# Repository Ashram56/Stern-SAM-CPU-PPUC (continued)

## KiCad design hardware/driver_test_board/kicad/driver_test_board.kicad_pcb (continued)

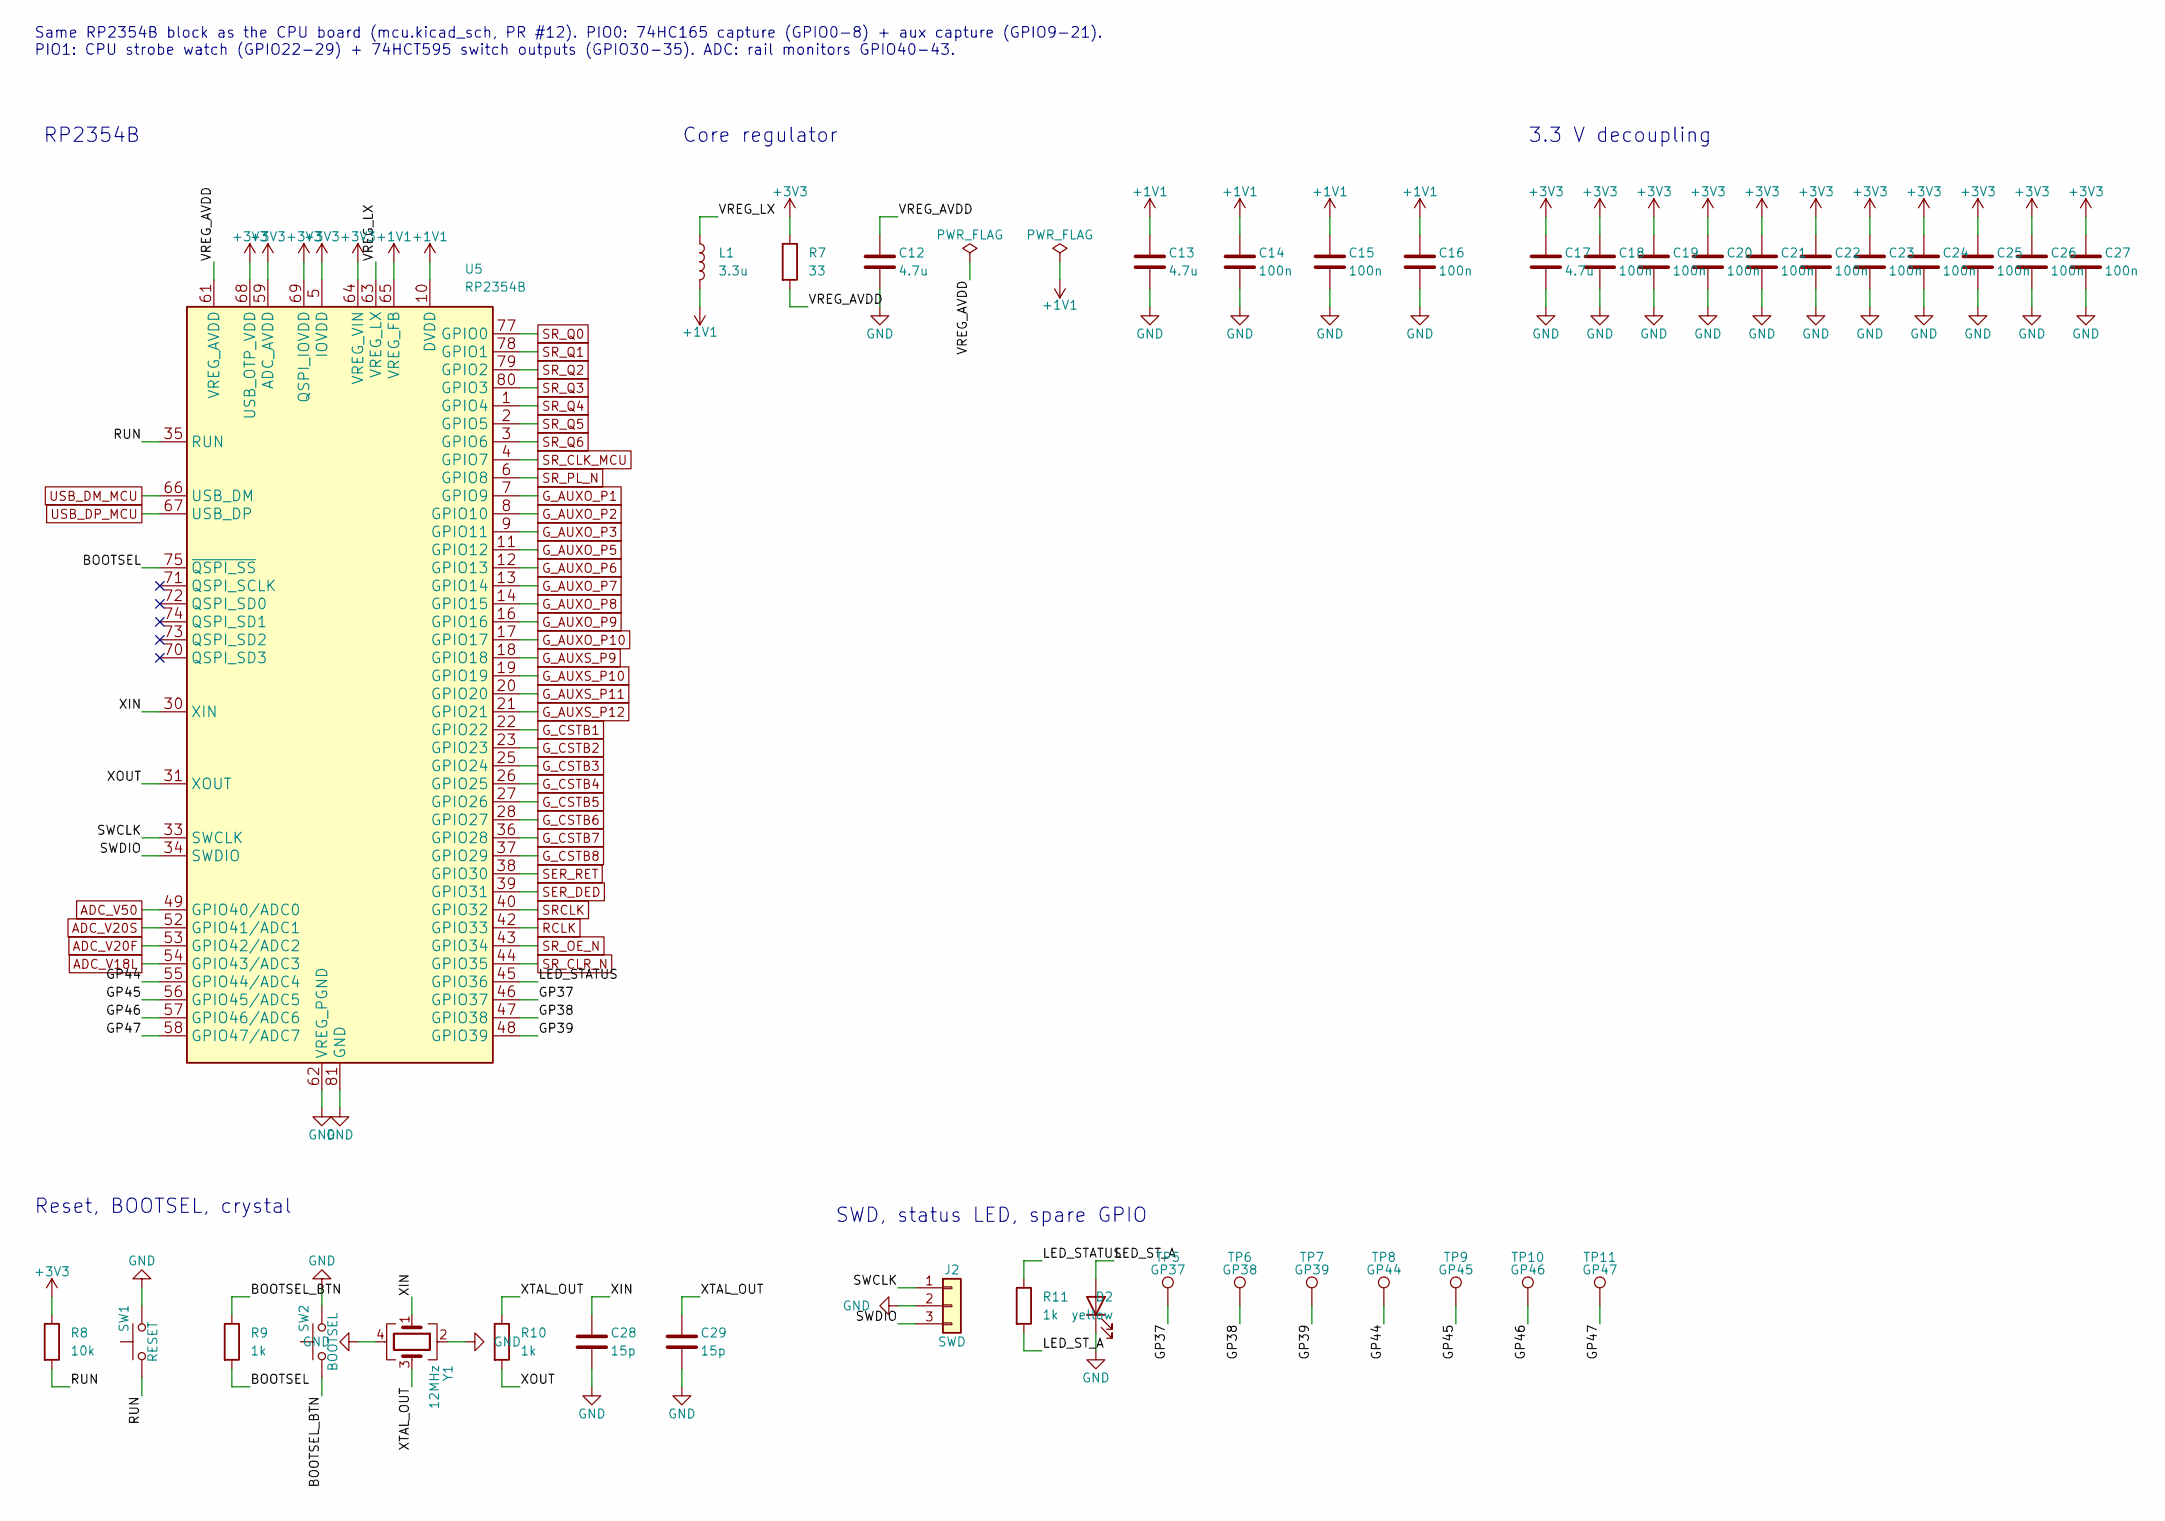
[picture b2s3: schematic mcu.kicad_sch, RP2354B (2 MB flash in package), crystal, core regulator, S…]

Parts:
C12, C13, C17: 4.7u; C_0805_2012Metric
C14, C15, C16, C18, C19, C20, C21, C22, C23, C24, C25, C26, C27: 100n; C_0805_2012Metric
C28, C29: 15p; C_0805_2012Metric
D2: yellow; LED_0805_2012Metric
J2: SWD; PinHeader_1x03_P2.54mm_Vertical
L1: 3.3u; L_Cenker_CKCS201610
R7: 33; R_0805_2012Metric
R8: 10k; R_0805_2012Metric
R9, R10, R11: 1k; R_0805_2012Metric
SW1: RESET; SW_SPST_TL3342
SW2: BOOTSEL; SW_SPST_TL3342
TP5: GP37; TestPoint_Pad_D1.5mm
TP6: GP38; TestPoint_Pad_D1.5mm
TP7: GP39; TestPoint_Pad_D1.5mm
TP8: GP44; TestPoint_Pad_D1.5mm
TP9: GP45; TestPoint_Pad_D1.5mm
TP10: GP46; TestPoint_Pad_D1.5mm
TP11: GP47; TestPoint_Pad_D1.5mm
U5: RP2354B; QFN-80-1EP_10x10mm_P0.4mm_EP3.4x3.4mm
Y1: 12MHz; Crystal_SMD_3225-4Pin_3.2x2.5mm

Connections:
+1V1: C13.1, C14.1, C15.1, C16.1, L1.2, U5.10 (DVDD), U5.32 (DVDD), U5.51 (DVDD), U5.65 (VREG_FB)
+3V3: C17.1, C18.1, C19.1, C20.1, C21.1, C22.1, C23.1, C24.1, C25.1, C26.1, C27.1, R7.1, R8.1, U5.5 (IOVDD), U5.15 (IOVDD), U5.24 (IOVDD), U5.29 (IOVDD), U5.41 (IOVDD), U5.50 (IOVDD), U5.59 (ADC_AVDD), U5.60 (IOVDD), U5.64 (VREG_VIN), U5.68 (USB_OTP_VDD), U5.69 (QSPI_IOVDD), U5.76 (IOVDD); also elsewhere on the board
/MCU/BOOTSEL: R9.2, U5.75 (~QSPI_SS)
/MCU/BOOTSEL_BTN: R9.1, SW2.1
/MCU/GP37: TP5.1, U5.46 (GPIO37)
/MCU/GP38: TP6.1, U5.47 (GPIO38)
/MCU/GP39: TP7.1, U5.48 (GPIO39)
/MCU/GP44: TP8.1, U5.55 (GPIO44/ADC4)
/MCU/GP45: TP9.1, U5.56 (GPIO45/ADC5)
/MCU/GP46: TP10.1, U5.57 (GPIO46/ADC6)
/MCU/GP47: TP11.1, U5.58 (GPIO47/ADC7)
/MCU/LED_STATUS: R11.1, U5.45 (GPIO36)
/MCU/LED_ST_A: D2.2 (A), R11.2
/MCU/RUN: R8.2, SW1.1, U5.35 (RUN)
/MCU/SWCLK: J2.1, U5.33 (SWCLK)
/MCU/SWDIO: J2.3, U5.34 (SWDIO)
/MCU/VREG_AVDD: C12.1, R7.2, U5.61 (VREG_AVDD)
/MCU/VREG_LX: L1.1, U5.63 (VREG_LX)
/MCU/XIN: C28.1, U5.30 (XIN), Y1.1
/MCU/XOUT: R10.2, U5.31 (XOUT)
/MCU/XTAL_OUT: C29.1, R10.1, Y1.3
ADC_V18L: U5.54 (GPIO43/ADC3); also elsewhere on the board
ADC_V20F: U5.53 (GPIO42/ADC2); also elsewhere on the board
ADC_V20S: U5.52 (GPIO41/ADC1); also elsewhere on the board
ADC_V50: U5.49 (GPIO40/ADC0); also elsewhere on the board
GND: C12.2, C13.2, C14.2, C15.2, C16.2, C17.2, C18.2, C19.2, C20.2, C21.2, C22.2, C23.2, C24.2, C25.2, C26.2, C27.2, C28.2, C29.2, D2.1 (K), J2.2, SW1.2, SW2.2, U5.62 (VREG_PGND), U5.81 (GND), Y1.2, Y1.4; also elsewhere on the board
G_AUXO_P1: U5.7 (GPIO9); also elsewhere on the board
G_AUXO_P2: U5.8 (GPIO10); also elsewhere on the board
G_AUXO_P3: U5.9 (GPIO11); also elsewhere on the board
G_AUXO_P5: U5.11 (GPIO12); also elsewhere on the board
G_AUXO_P6: U5.12 (GPIO13); also elsewhere on the board
G_AUXO_P7: U5.13 (GPIO14); also elsewhere on the board
G_AUXO_P8: U5.14 (GPIO15); also elsewhere on the board
G_AUXO_P9: U5.16 (GPIO16); also elsewhere on the board
G_AUXO_P10: U5.17 (GPIO17); also elsewhere on the board
G_AUXS_P9: U5.18 (GPIO18); also elsewhere on the board
G_AUXS_P10: U5.19 (GPIO19); also elsewhere on the board
G_AUXS_P11: U5.20 (GPIO20); also elsewhere on the board
G_AUXS_P12: U5.21 (GPIO21); also elsewhere on the board
G_CSTB1: U5.22 (GPIO22); also elsewhere on the board
G_CSTB2: U5.23 (GPIO23); also elsewhere on the board
G_CSTB3: U5.25 (GPIO24); also elsewhere on the board
G_CSTB4: U5.26 (GPIO25); also elsewhere on the board
G_CSTB5: U5.27 (GPIO26); also elsewhere on the board
G_CSTB6: U5.28 (GPIO27); also elsewhere on the board
G_CSTB7: U5.36 (GPIO28); also elsewhere on the board
G_CSTB8: U5.37 (GPIO29); also elsewhere on the board
RCLK: U5.42 (GPIO33); also elsewhere on the board
SER_DED: U5.39 (GPIO31); also elsewhere on the board
SER_RET: U5.38 (GPIO30); also elsewhere on the board
SRCLK: U5.40 (GPIO32); also elsewhere on the board
SR_CLK_MCU: U5.4 (GPIO7); also elsewhere on the board
SR_CLR_N: U5.44 (GPIO35); also elsewhere on the board
SR_OE_N: U5.43 (GPIO34); also elsewhere on the board
SR_PL_N: U5.6 (GPIO8); also elsewhere on the board
SR_Q0: U5.77 (GPIO0); also elsewhere on the board
SR_Q1: U5.78 (GPIO1); also elsewhere on the board
SR_Q2: U5.79 (GPIO2); also elsewhere on the board
SR_Q3: U5.80 (GPIO3); also elsewhere on the board
SR_Q4: U5.1 (GPIO4); also elsewhere on the board
SR_Q5: U5.2 (GPIO5); also elsewhere on the board
SR_Q6: U5.3 (GPIO6); also elsewhere on the board
USB_DM_MCU: U5.66 (USB_DM); also elsewhere on the board
USB_DP_MCU: U5.67 (USB_DP); also elsewhere on the board

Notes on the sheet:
Same RP2354B block as the CPU board (mcu.kicad_sch, PR #12). PIO0: 74HC165 capture (GPIO0-8) + aux capture (GPIO9-21). PIO1: CPU strobe watch (GPIO22-29) + 74HCT595 switch outputs (GPIO30-35). ADC: rail monitors GPIO40-43.
RP2354B
Core regulator
3.3 V decoupling
Reset, BOOTSEL, crystal
SWD, status LED, spare GPIO

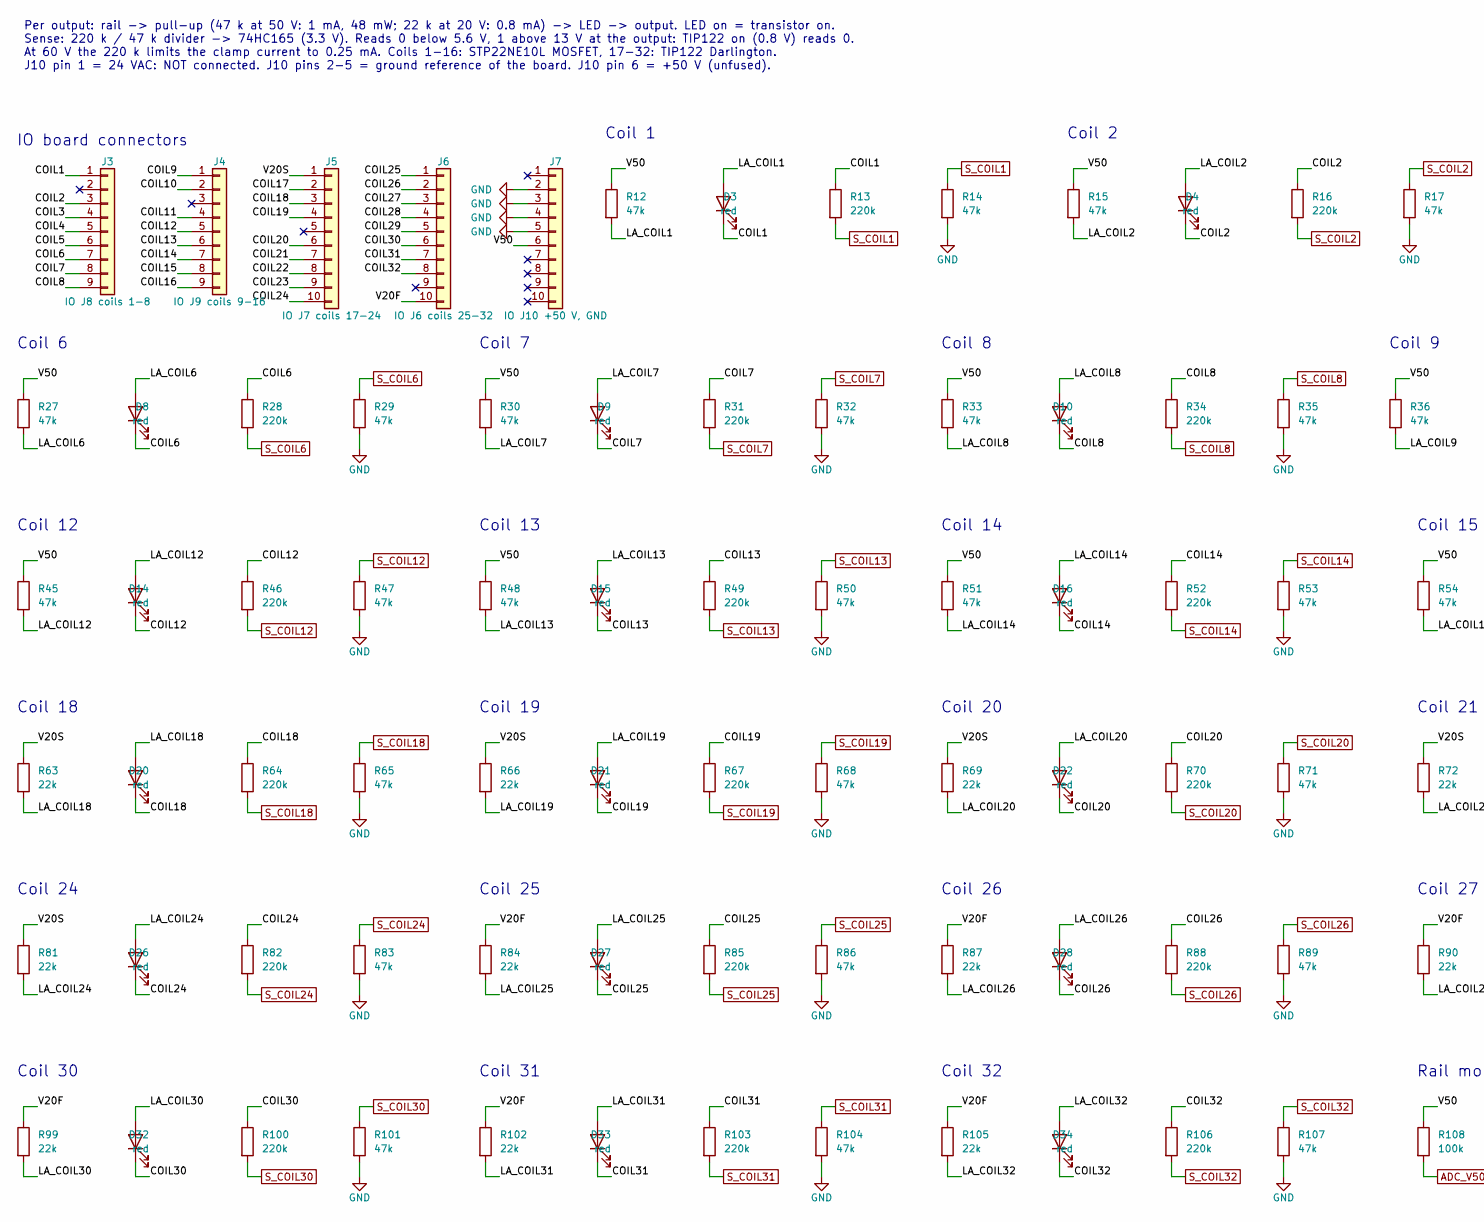
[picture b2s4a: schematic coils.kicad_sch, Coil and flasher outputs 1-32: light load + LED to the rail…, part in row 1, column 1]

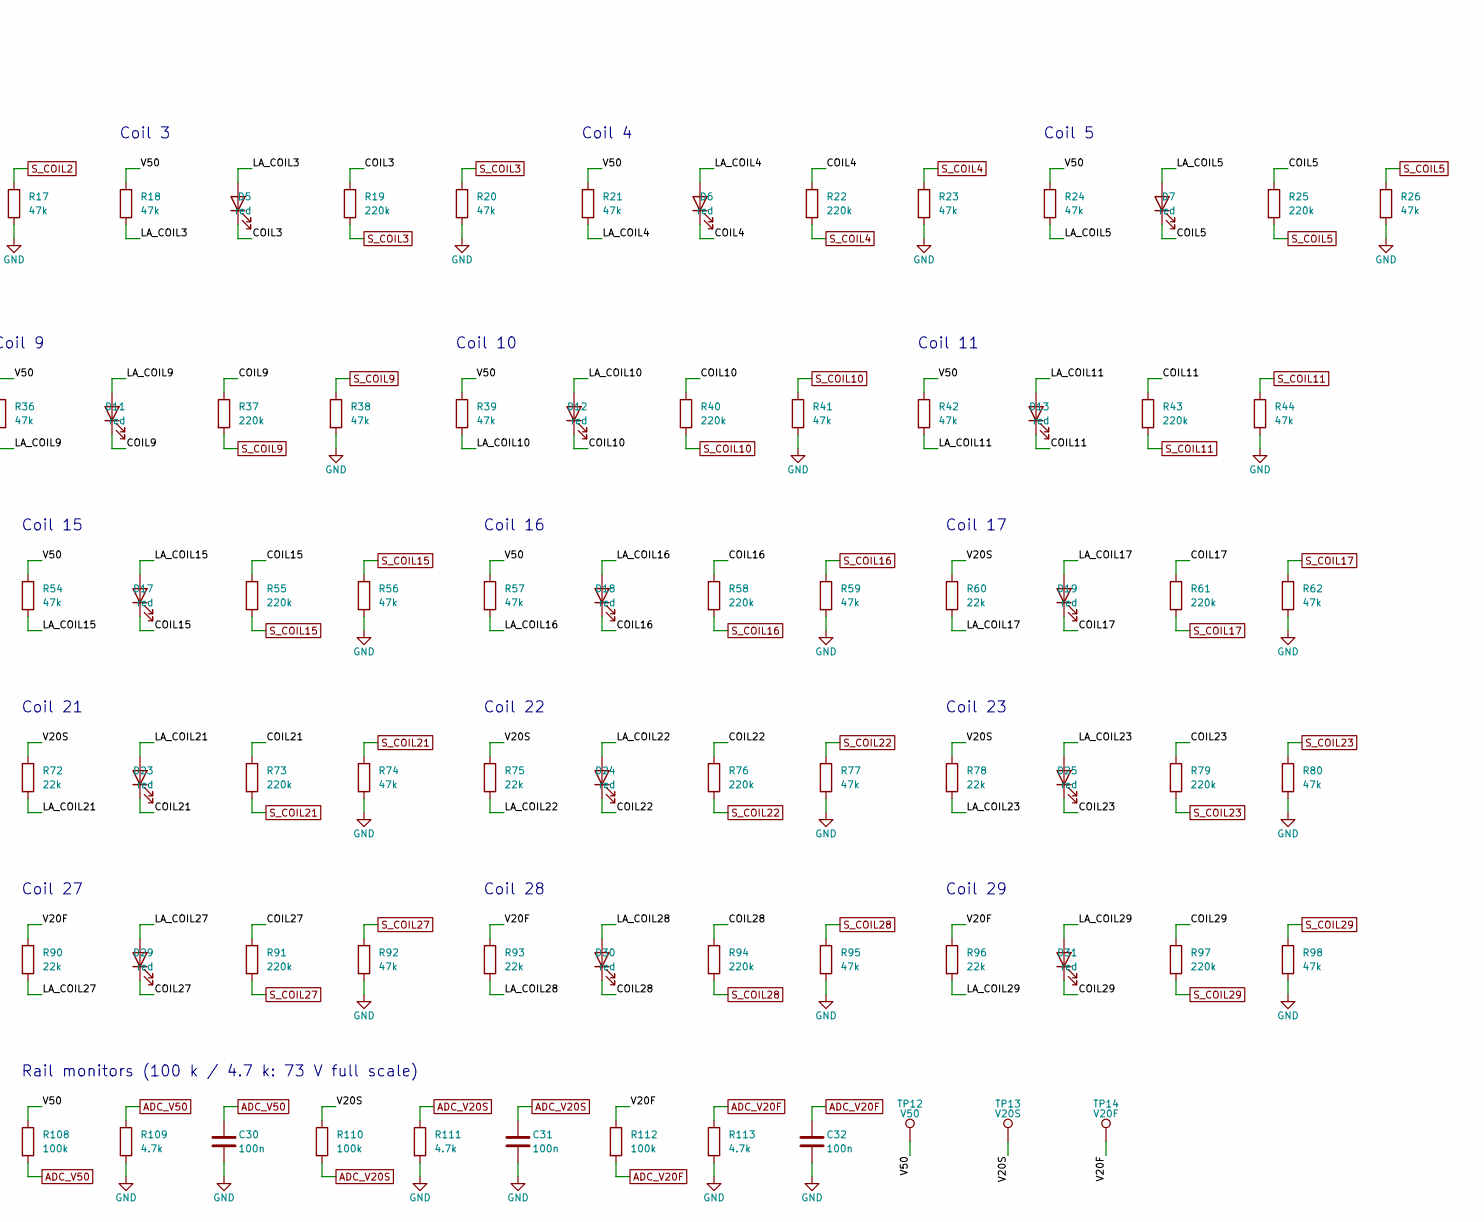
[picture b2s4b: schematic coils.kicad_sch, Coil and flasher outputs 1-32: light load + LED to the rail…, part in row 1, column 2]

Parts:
C30, C31, C32: 100n; C_0805_2012Metric
D3, D4, D5, D6, D7, D8, D9, D10, D11, D12, D13, D14, D15, D16, D17, D18, D19, D20, D21, D22, D23, D24, D25, D26, D27, D28, D29, D30, D31, D32, D33, D34: red; LED_0805_2012Metric
J3: IO J8 coils 1-8; Molex_KK-396_A-41791-0009_1x09_P3.96mm_Vertical
J4: IO J9 coils 9-16; Molex_KK-396_A-41791-0009_1x09_P3.96mm_Vertical
J5: IO J7 coils 17-24; Molex_KK-396_A-41791-0010_1x10_P3.96mm_Vertical
J6: IO J6 coils 25-32; Molex_KK-396_A-41791-0010_1x10_P3.96mm_Vertical
J7: IO J10 +50 V, GND; Molex_KK-396_A-41791-0010_1x10_P3.96mm_Vertical
R12, R14, R15, R17, R18, R20, R21, R23, R24, R26, R27, R29, R30, R32, R33, R35, R36, R38, R39, R41, R42, R44, R45, R47, R48, R50, R51, R53, R54, R56, R57, R59, R62, R65, R68, R71, R74, R77, R80, R83, R86, R89, R92, R95, R98, R101, R104, R107: 47k; R_0805_2012Metric
R13, R16, R19, R22, R25, R28, R31, R34, R37, R40, R43, R46, R49, R52, R55, R58, R61, R64, R67, R70, R73, R76, R79, R82, R85, R88, R91, R94, R97, R100, R103, R106: 220k; R_0805_2012Metric
R60, R63, R66, R69, R72, R75, R78, R81, R84, R87, R90, R93, R96, R99, R102, R105: 22k; R_0805_2012Metric
R108, R110, R112: 100k; R_0805_2012Metric
R109, R111, R113: 4.7k; R_0805_2012Metric
TP12: V50; TestPoint_Pad_D1.5mm
TP13: V20S; TestPoint_Pad_D1.5mm
TP14: V20F; TestPoint_Pad_D1.5mm

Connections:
/Coil outputs/COIL1: D3.1 (K), J3.1, R13.1
/Coil outputs/COIL2: D4.1 (K), J3.3, R16.1
/Coil outputs/COIL3: D5.1 (K), J3.4, R19.1
/Coil outputs/COIL4: D6.1 (K), J3.5, R22.1
/Coil outputs/COIL5: D7.1 (K), J3.6, R25.1
/Coil outputs/COIL6: D8.1 (K), J3.7, R28.1
/Coil outputs/COIL7: D9.1 (K), J3.8, R31.1
/Coil outputs/COIL8: D10.1 (K), J3.9, R34.1
/Coil outputs/COIL9: D11.1 (K), J4.1, R37.1
/Coil outputs/COIL10: D12.1 (K), J4.2, R40.1
/Coil outputs/COIL11: D13.1 (K), J4.4, R43.1
/Coil outputs/COIL12: D14.1 (K), J4.5, R46.1
/Coil outputs/COIL13: D15.1 (K), J4.6, R49.1
/Coil outputs/COIL14: D16.1 (K), J4.7, R52.1
/Coil outputs/COIL15: D17.1 (K), J4.8, R55.1
/Coil outputs/COIL16: D18.1 (K), J4.9, R58.1
/Coil outputs/COIL17: D19.1 (K), J5.2, R61.1
/Coil outputs/COIL18: D20.1 (K), J5.3, R64.1
/Coil outputs/COIL19: D21.1 (K), J5.4, R67.1
/Coil outputs/COIL20: D22.1 (K), J5.6, R70.1
/Coil outputs/COIL21: D23.1 (K), J5.7, R73.1
/Coil outputs/COIL22: D24.1 (K), J5.8, R76.1
/Coil outputs/COIL23: D25.1 (K), J5.9, R79.1
/Coil outputs/COIL24: D26.1 (K), J5.10, R82.1
/Coil outputs/COIL25: D27.1 (K), J6.1, R85.1
/Coil outputs/COIL26: D28.1 (K), J6.2, R88.1
/Coil outputs/COIL27: D29.1 (K), J6.3, R91.1
/Coil outputs/COIL28: D30.1 (K), J6.4, R94.1
/Coil outputs/COIL29: D31.1 (K), J6.5, R97.1
/Coil outputs/COIL30: D32.1 (K), J6.6, R100.1
/Coil outputs/COIL31: D33.1 (K), J6.7, R103.1
/Coil outputs/COIL32: D34.1 (K), J6.8, R106.1
/Coil outputs/LA_COIL1: D3.2 (A), R12.2
/Coil outputs/LA_COIL2: D4.2 (A), R15.2
/Coil outputs/LA_COIL3: D5.2 (A), R18.2
/Coil outputs/LA_COIL4: D6.2 (A), R21.2
/Coil outputs/LA_COIL5: D7.2 (A), R24.2
/Coil outputs/LA_COIL6: D8.2 (A), R27.2
/Coil outputs/LA_COIL7: D9.2 (A), R30.2
/Coil outputs/LA_COIL8: D10.2 (A), R33.2
/Coil outputs/LA_COIL9: D11.2 (A), R36.2
/Coil outputs/LA_COIL10: D12.2 (A), R39.2
/Coil outputs/LA_COIL11: D13.2 (A), R42.2
/Coil outputs/LA_COIL12: D14.2 (A), R45.2
/Coil outputs/LA_COIL13: D15.2 (A), R48.2
/Coil outputs/LA_COIL14: D16.2 (A), R51.2
/Coil outputs/LA_COIL15: D17.2 (A), R54.2
/Coil outputs/LA_COIL16: D18.2 (A), R57.2
/Coil outputs/LA_COIL17: D19.2 (A), R60.2
/Coil outputs/LA_COIL18: D20.2 (A), R63.2
/Coil outputs/LA_COIL19: D21.2 (A), R66.2
/Coil outputs/LA_COIL20: D22.2 (A), R69.2
/Coil outputs/LA_COIL21: D23.2 (A), R72.2
/Coil outputs/LA_COIL22: D24.2 (A), R75.2
/Coil outputs/LA_COIL23: D25.2 (A), R78.2
/Coil outputs/LA_COIL24: D26.2 (A), R81.2
/Coil outputs/LA_COIL25: D27.2 (A), R84.2
/Coil outputs/LA_COIL26: D28.2 (A), R87.2
/Coil outputs/LA_COIL27: D29.2 (A), R90.2
/Coil outputs/LA_COIL28: D30.2 (A), R93.2
/Coil outputs/LA_COIL29: D31.2 (A), R96.2
/Coil outputs/LA_COIL30: D32.2 (A), R99.2
/Coil outputs/LA_COIL31: D33.2 (A), R102.2
/Coil outputs/LA_COIL32: D34.2 (A), R105.2
/Coil outputs/V20F: J6.10, R84.1, R87.1, R90.1, R93.1, R96.1, R99.1, R102.1, R105.1, R112.1, TP14.1
/Coil outputs/V20S: J5.1, R60.1, R63.1, R66.1, R69.1, R72.1, R75.1, R78.1, R81.1, R110.1, TP13.1
/Coil outputs/V50: J7.6, R12.1, R15.1, R18.1, R21.1, R24.1, R27.1, R30.1, R33.1, R36.1, R39.1, R42.1, R45.1, R48.1, R51.1, R54.1, R57.1, R108.1, TP12.1
ADC_V20F: C32.1, R112.2, R113.1; also elsewhere on the board
ADC_V20S: C31.1, R110.2, R111.1; also elsewhere on the board
ADC_V50: C30.1, R108.2, R109.1; also elsewhere on the board
GND: C30.2, C31.2, C32.2, J7.2, J7.3, J7.4, J7.5, R14.2, R17.2, R20.2, R23.2, R26.2, R29.2, R32.2, R35.2, R38.2, R41.2, R44.2, R47.2, R50.2, R53.2, R56.2, R59.2, R62.2, R65.2, R68.2, R71.2, R74.2, R77.2, R80.2, R83.2, R86.2, R89.2, R92.2, R95.2, R98.2, R101.2, R104.2, R107.2, R109.2, R111.2, R113.2; also elsewhere on the board
S_COIL1: R13.2, R14.1; also elsewhere on the board
S_COIL2: R16.2, R17.1; also elsewhere on the board
S_COIL3: R19.2, R20.1; also elsewhere on the board
S_COIL4: R22.2, R23.1; also elsewhere on the board
S_COIL5: R25.2, R26.1; also elsewhere on the board
S_COIL6: R28.2, R29.1; also elsewhere on the board
S_COIL7: R31.2, R32.1; also elsewhere on the board
S_COIL8: R34.2, R35.1; also elsewhere on the board
S_COIL9: R37.2, R38.1; also elsewhere on the board
S_COIL10: R40.2, R41.1; also elsewhere on the board
S_COIL11: R43.2, R44.1; also elsewhere on the board
S_COIL12: R46.2, R47.1; also elsewhere on the board
S_COIL13: R49.2, R50.1; also elsewhere on the board
S_COIL14: R52.2, R53.1; also elsewhere on the board
S_COIL15: R55.2, R56.1; also elsewhere on the board
S_COIL16: R58.2, R59.1; also elsewhere on the board
S_COIL17: R61.2, R62.1; also elsewhere on the board
S_COIL18: R64.2, R65.1; also elsewhere on the board
S_COIL19: R67.2, R68.1; also elsewhere on the board
S_COIL20: R70.2, R71.1; also elsewhere on the board
S_COIL21: R73.2, R74.1; also elsewhere on the board
S_COIL22: R76.2, R77.1; also elsewhere on the board
S_COIL23: R79.2, R80.1; also elsewhere on the board
S_COIL24: R82.2, R83.1; also elsewhere on the board
S_COIL25: R85.2, R86.1; also elsewhere on the board
S_COIL26: R88.2, R89.1; also elsewhere on the board
S_COIL27: R91.2, R92.1; also elsewhere on the board
S_COIL28: R94.2, R95.1; also elsewhere on the board
S_COIL29: R97.2, R98.1; also elsewhere on the board
S_COIL30: R100.2, R101.1; also elsewhere on the board
S_COIL31: R103.2, R104.1; also elsewhere on the board
S_COIL32: R106.2, R107.1; also elsewhere on the board

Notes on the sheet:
Per output: rail -> pull-up (47 k at 50 V: 1 mA, 48 mW; 22 k at 20 V: 0.8 mA) -> LED -> output. LED on = transistor on. Sense: 220 k / 47 k divider -> 74HC165 (3.3 V). Reads 0 below 5.6 V, 1 above 13 V at the output: TIP122 on (0.8 V) reads 0. At 60 V the 220 k limits the clamp current to 0.25 mA. 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
IO board connectors
Coil 1
Coil 2
Coil 3
Coil 4
Coil 5
Coil 6
Coil 7
Coil 8
Coil 9
Coil 10
Coil 11
Coil 12
Coil 13
Coil 14
Coil 15
Coil 16
Coil 17
Coil 18
Coil 19
Coil 20
Coil 21
Coil 22
Coil 23
Coil 24
Coil 25
Coil 26
Coil 27
Coil 28
Coil 29
Coil 30
Coil 31
Coil 32
Rail monitors (100 k / 4.7 k: 73 V full scale)

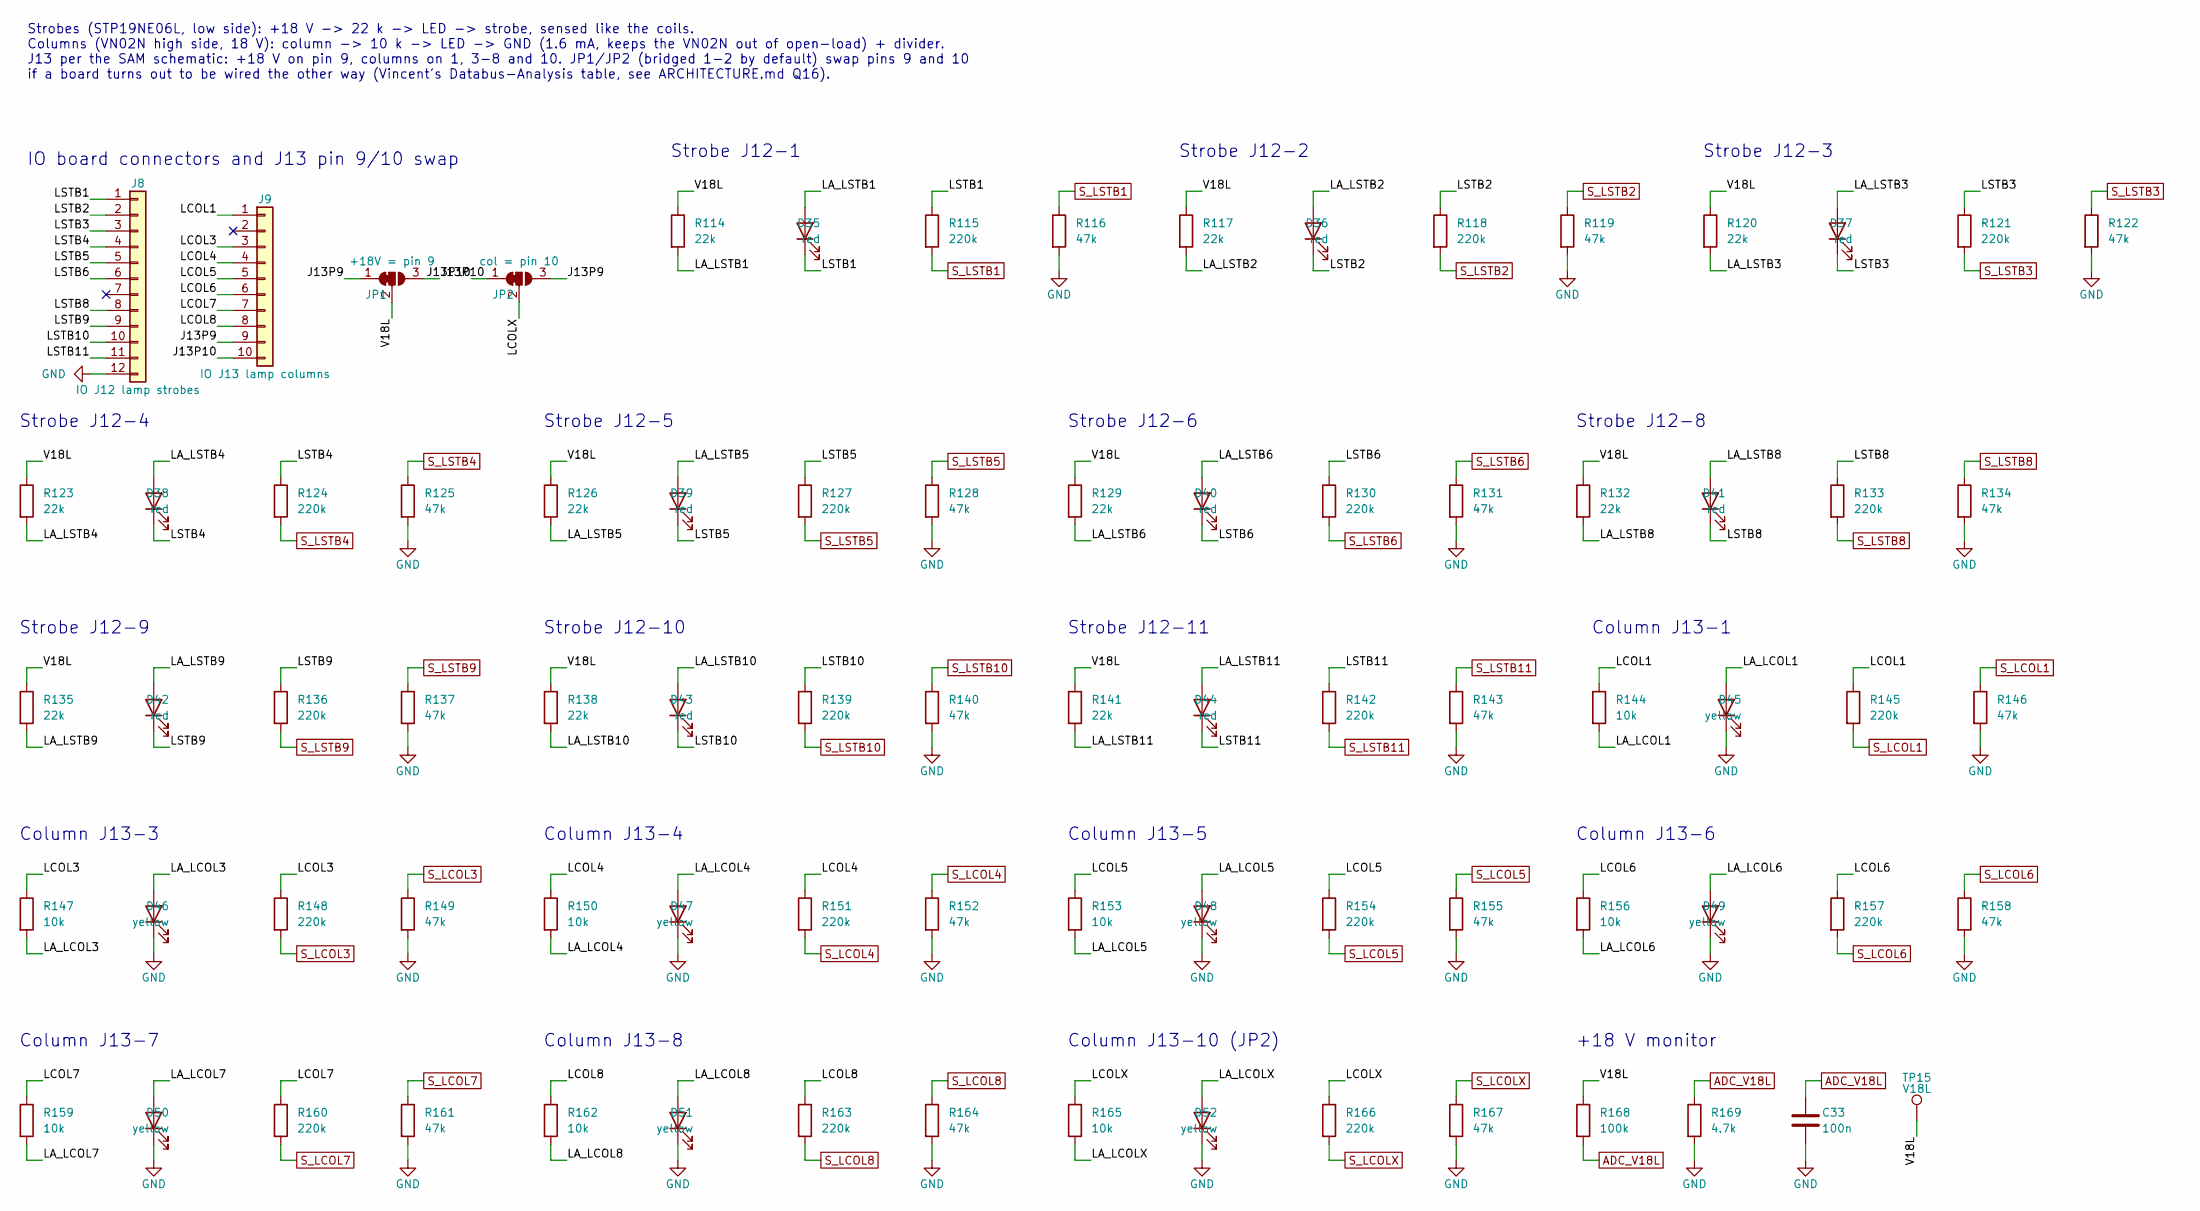
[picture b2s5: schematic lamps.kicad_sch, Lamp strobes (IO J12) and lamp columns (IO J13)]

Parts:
C33: 100n; C_0805_2012Metric
D35, D36, D37, D38, D39, D40, D41, D42, D43, D44: red; LED_0805_2012Metric
D45, D46, D47, D48, D49, D50, D51, D52: yellow; LED_0805_2012Metric
J8: IO J12 lamp strobes; Molex_KK-396_A-41791-0012_1x12_P3.96mm_Vertical
J9: IO J13 lamp columns; Molex_KK-396_A-41791-0010_1x10_P3.96mm_Vertical
JP1: +18V = pin 9; SolderJumper-3_P1.3mm_Bridged12_RoundedPad1.0x1.5mm
JP2: col = pin 10; SolderJumper-3_P1.3mm_Bridged12_RoundedPad1.0x1.5mm
R114, R117, R120, R123, R126, R129, R132, R135, R138, R141: 22k; R_0805_2012Metric
R115, R118, R121, R124, R127, R130, R133, R136, R139, R142, R145, R148, R151, R154, R157, R160, R163, R166: 220k; R_0805_2012Metric
R116, R119, R122, R125, R128, R131, R134, R137, R140, R143, R146, R149, R152, R155, R158, R161, R164, R167: 47k; R_0805_2012Metric
R144, R147, R150, R153, R156, R159, R162, R165: 10k; R_0805_2012Metric
R168: 100k; R_0805_2012Metric
R169: 4.7k; R_0805_2012Metric
TP15: V18L; TestPoint_Pad_D1.5mm

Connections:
/Lamp matrix/J13P9: J9.9, JP1.1 (A), JP2.3 (B)
/Lamp matrix/J13P10: J9.10, JP1.3 (B), JP2.1 (A)
/Lamp matrix/LA_LCOL1: D45.2 (A), R144.2
/Lamp matrix/LA_LCOL3: D46.2 (A), R147.2
/Lamp matrix/LA_LCOL4: D47.2 (A), R150.2
/Lamp matrix/LA_LCOL5: D48.2 (A), R153.2
/Lamp matrix/LA_LCOL6: D49.2 (A), R156.2
/Lamp matrix/LA_LCOL7: D50.2 (A), R159.2
/Lamp matrix/LA_LCOL8: D51.2 (A), R162.2
/Lamp matrix/LA_LCOLX: D52.2 (A), R165.2
/Lamp matrix/LA_LSTB1: D35.2 (A), R114.2
/Lamp matrix/LA_LSTB2: D36.2 (A), R117.2
/Lamp matrix/LA_LSTB3: D37.2 (A), R120.2
/Lamp matrix/LA_LSTB4: D38.2 (A), R123.2
/Lamp matrix/LA_LSTB5: D39.2 (A), R126.2
/Lamp matrix/LA_LSTB6: D40.2 (A), R129.2
/Lamp matrix/LA_LSTB8: D41.2 (A), R132.2
/Lamp matrix/LA_LSTB9: D42.2 (A), R135.2
/Lamp matrix/LA_LSTB10: D43.2 (A), R138.2
/Lamp matrix/LA_LSTB11: D44.2 (A), R141.2
/Lamp matrix/LCOL1: J9.1, R144.1, R145.1
/Lamp matrix/LCOL3: J9.3, R147.1, R148.1
/Lamp matrix/LCOL4: J9.4, R150.1, R151.1
/Lamp matrix/LCOL5: J9.5, R153.1, R154.1
/Lamp matrix/LCOL6: J9.6, R156.1, R157.1
/Lamp matrix/LCOL7: J9.7, R159.1, R160.1
/Lamp matrix/LCOL8: J9.8, R162.1, R163.1
/Lamp matrix/LCOLX: JP2.2 (C), R165.1, R166.1
/Lamp matrix/LSTB1: D35.1 (K), J8.1, R115.1
/Lamp matrix/LSTB2: D36.1 (K), J8.2, R118.1
/Lamp matrix/LSTB3: D37.1 (K), J8.3, R121.1
/Lamp matrix/LSTB4: D38.1 (K), J8.4, R124.1
/Lamp matrix/LSTB5: D39.1 (K), J8.5, R127.1
/Lamp matrix/LSTB6: D40.1 (K), J8.6, R130.1
/Lamp matrix/LSTB8: D41.1 (K), J8.8, R133.1
/Lamp matrix/LSTB9: D42.1 (K), J8.9, R136.1
/Lamp matrix/LSTB10: D43.1 (K), J8.10, R139.1
/Lamp matrix/LSTB11: D44.1 (K), J8.11, R142.1
/Lamp matrix/V18L: JP1.2 (C), R114.1, R117.1, R120.1, R123.1, R126.1, R129.1, R132.1, R135.1, R138.1, R141.1, R168.1, TP15.1
ADC_V18L: C33.1, R168.2, R169.1; also elsewhere on the board
GND: C33.2, D45.1 (K), D46.1 (K), D47.1 (K), D48.1 (K), D49.1 (K), D50.1 (K), D51.1 (K), D52.1 (K), J8.12, R116.2, R119.2, R122.2, R125.2, R128.2, R131.2, R134.2, R137.2, R140.2, R143.2, R146.2, R149.2, R152.2, R155.2, R158.2, R161.2, R164.2, R167.2, R169.2; also elsewhere on the board
S_LCOL1: R145.2, R146.1; also elsewhere on the board
S_LCOL3: R148.2, R149.1; also elsewhere on the board
S_LCOL4: R151.2, R152.1; also elsewhere on the board
S_LCOL5: R154.2, R155.1; also elsewhere on the board
S_LCOL6: R157.2, R158.1; also elsewhere on the board
S_LCOL7: R160.2, R161.1; also elsewhere on the board
S_LCOL8: R163.2, R164.1; also elsewhere on the board
S_LCOLX: R166.2, R167.1; also elsewhere on the board
S_LSTB1: R115.2, R116.1; also elsewhere on the board
S_LSTB2: R118.2, R119.1; also elsewhere on the board
S_LSTB3: R121.2, R122.1; also elsewhere on the board
S_LSTB4: R124.2, R125.1; also elsewhere on the board
S_LSTB5: R127.2, R128.1; also elsewhere on the board
S_LSTB6: R130.2, R131.1; also elsewhere on the board
S_LSTB8: R133.2, R134.1; also elsewhere on the board
S_LSTB9: R136.2, R137.1; also elsewhere on the board
S_LSTB10: R139.2, R140.1; also elsewhere on the board
S_LSTB11: R142.2, R143.1; also elsewhere on the board

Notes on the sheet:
Strobes (STP19NE06L, low side): +18 V -> 22 k -> LED -> strobe, sensed like the coils. Columns (VN02N high side, 18 V): column -> 10 k -> LED -> GND (1.6 mA, keeps the VN02N out of open-load) + divider. J13 per the SAM schematic: +18 V on pin 9, columns on 1, 3-8 and 10. JP1/JP2 (bridged 1-2 by def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
IO board connectors and J13 pin 9/10 swap
Strobe J12-1
Strobe J12-2
Strobe J12-3
Strobe J12-4
Strobe J12-5
Strobe J12-6
Strobe J12-8
Strobe J12-9
Strobe J12-10
Strobe J12-11
Column J13-1
Column J13-3
Column J13-4
Column J13-5
Column J13-6
Column J13-7
Column J13-8
Column J13-10 (JP2)
+18 V monitor
